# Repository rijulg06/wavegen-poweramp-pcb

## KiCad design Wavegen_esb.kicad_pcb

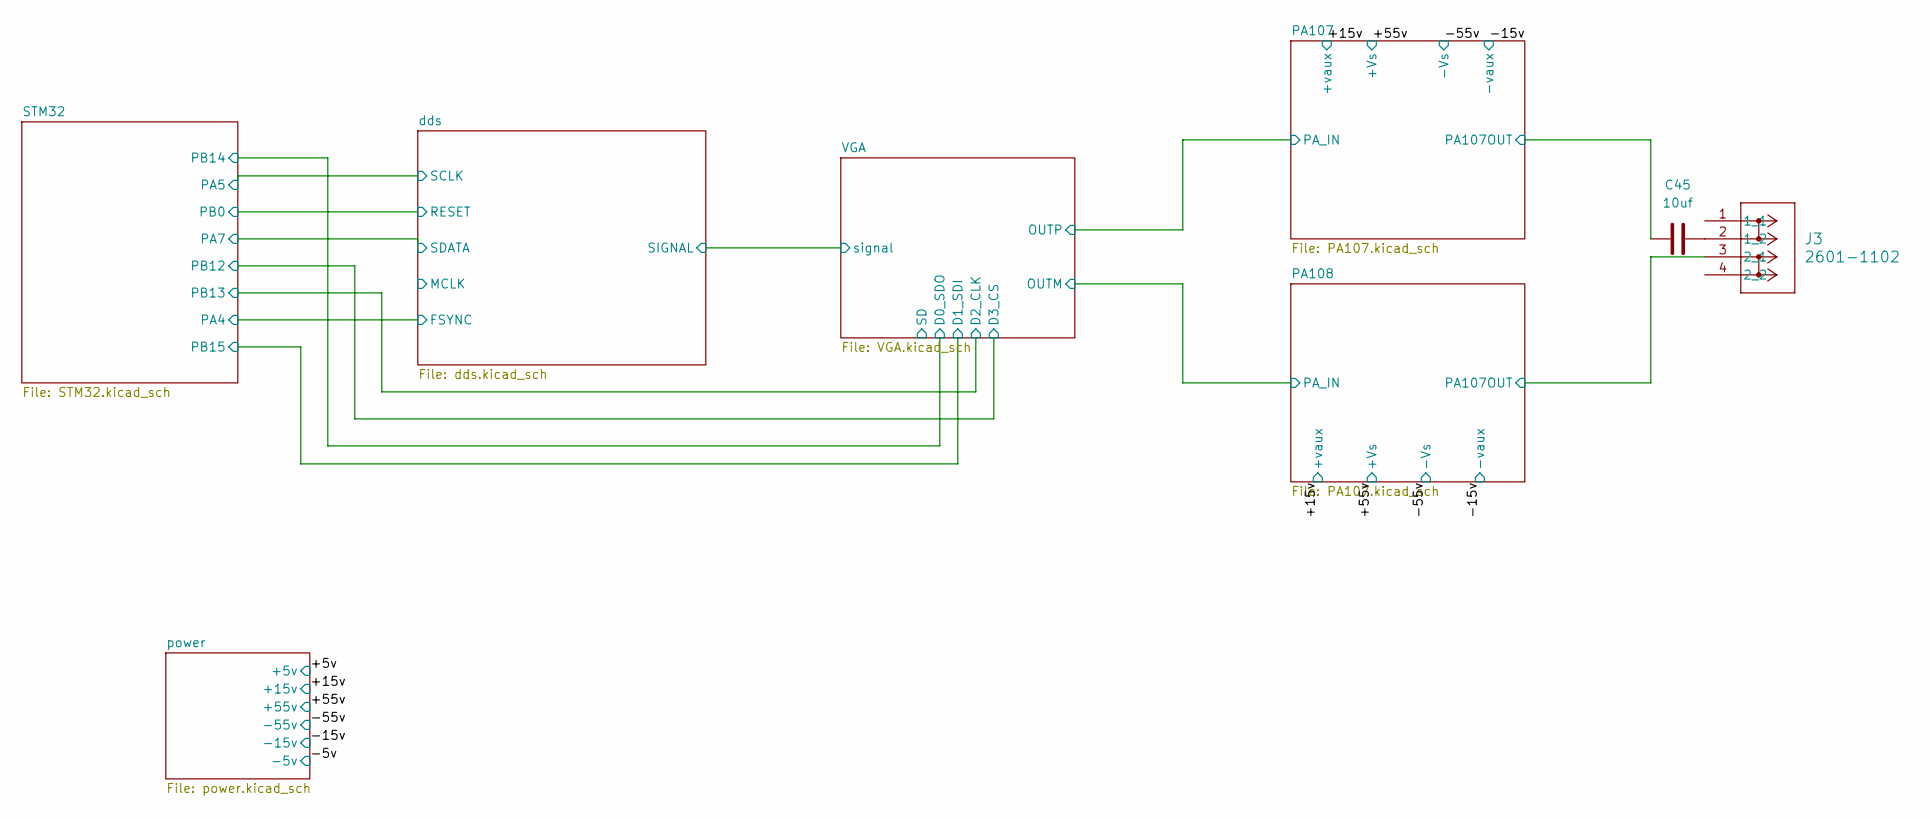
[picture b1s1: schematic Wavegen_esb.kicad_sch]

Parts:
C45: 10uf; CAPRR1500W80L2600T1150H2600
J3: 2601-1102; CONN2_2601-1102_WAG

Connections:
/PA107/PA107OUT: C45.2; also elsewhere on the board
/PA108/PA107OUT: J3.3 (2_1); also elsewhere on the board
unnamed: C45.1, J3.2 (1_2)

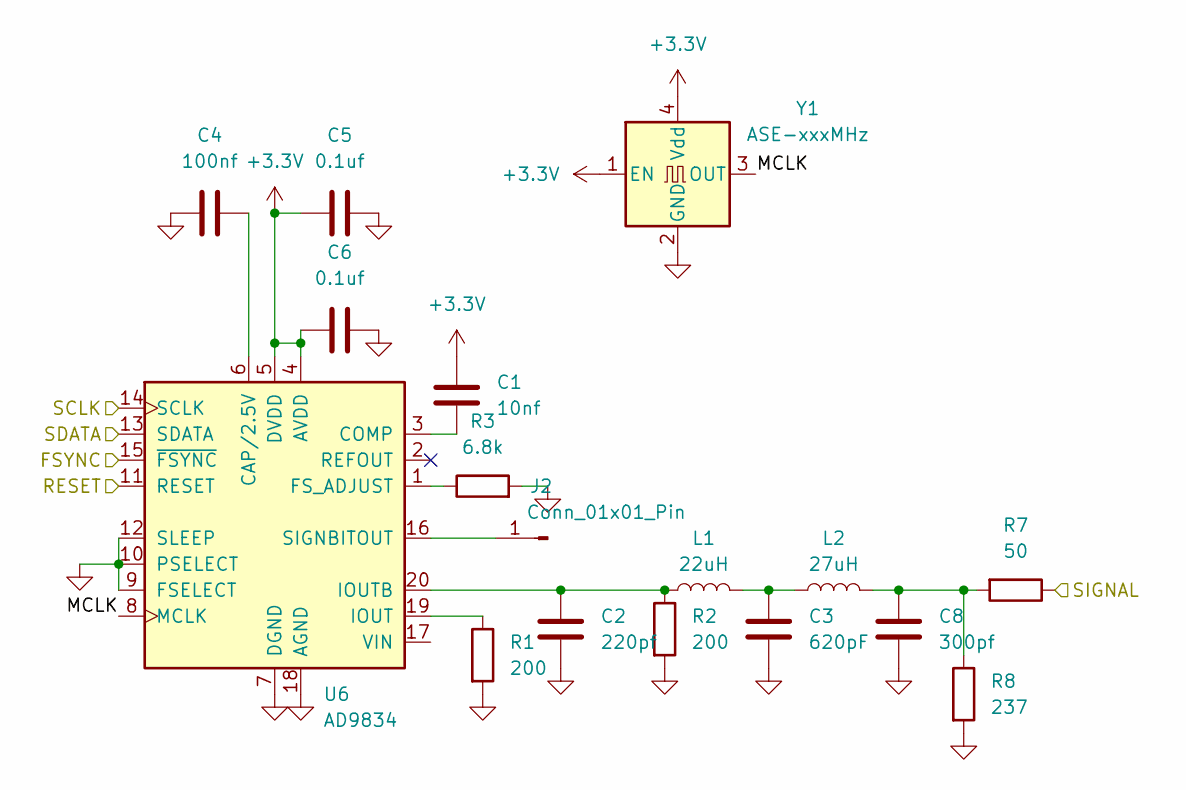
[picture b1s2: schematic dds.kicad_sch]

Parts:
C1: 10nf; C_0201_0603Metric
C2: 220pf; C_0201_0603Metric
C3: 620pF; C_0201_0603Metric
C4: 100nf; C_0201_0603Metric
C5, C6: 0.1uf; C_0201_0603Metric
C8: 300pf; C_0201_0603Metric
J2: Conn_01x01_Pin; TestPoint_Pad_1.5x1.5mm
L1: 22uH; IND_LSQM_B201616_TAY
L2: 27uH; IND_LSQM_B201616_TAY
R1, R2: 200; R_0201_0603Metric
R3: 6.8k; R_0201_0603Metric
R7: 50; R_0201_0603Metric
R8: 237; R_0201_0603Metric
U6: AD9834; TSSOP-20_4.4x6.5mm_P0.65mm
Y1: ASE-xxxMHz; Oscillator_SMD_Abracon_ASE-4Pin_3.2x2.5mm

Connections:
+3.3V: C1.2, C5.1, C6.1, U6.4 (AVDD), U6.5 (DVDD), Y1.1 (EN), Y1.4 (Vdd); also elsewhere on the board
/STM32/PA4: U6.15 (~FSYNC); also elsewhere on the board
/STM32/PA5: U6.14 (SCLK); also elsewhere on the board
/STM32/PA7: U6.13 (SDATA); also elsewhere on the board
/STM32/PB0: U6.11 (RESET); also elsewhere on the board
/VGA/signal: R7.1; also elsewhere on the board
/dds/MCLK: U6.8 (MCLK), Y1.3 (OUT)
GND: C2.1, C3.1, C4.1, C5.2, C6.2, C8.1, R1.2, R2.2, R3.2, R8.2, U6.7 (DGND), U6.9 (FSELECT), U6.10 (PSELECT), U6.12 (SLEEP), U6.18 (AGND), Y1.2 (GND); also elsewhere on the board
unnamed: C3.2, L1.2, L2.1
unnamed: C8.2, L2.2, R7.2, R8.1
unnamed: J2.1, U6.16 (SIGNBITOUT)
unnamed: C4.2, U6.6 (CAP/2.5V)
unnamed: C1.1, U6.3 (COMP)
unnamed: R3.1, U6.1 (FS_ADJUST)
unnamed: R1.1, U6.19 (IOUT)
unnamed: C2.2, L1.1, R2.1, U6.20 (IOUTB)

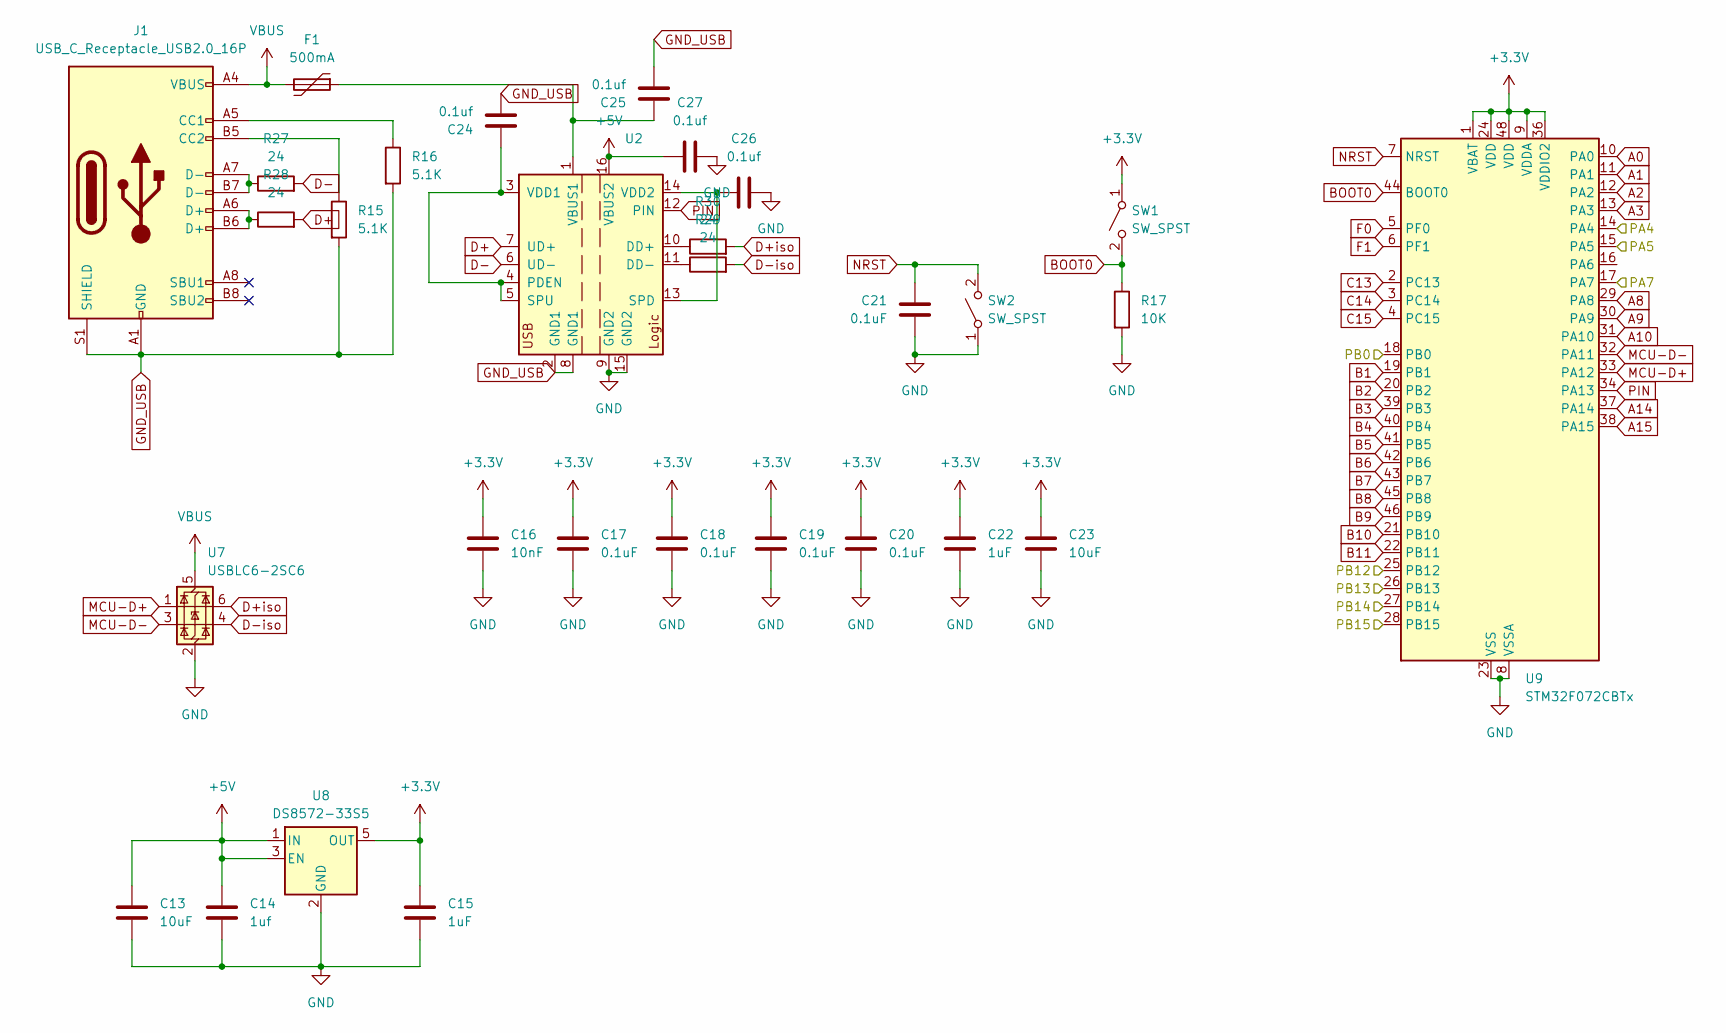
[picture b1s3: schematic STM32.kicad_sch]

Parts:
C13, C23: 10uF; C_0201_0603Metric
C14: 1uf; C_0201_0603Metric
C15, C22: 1uF; C_0201_0603Metric
C16: 10nF; C_0201_0603Metric
C17, C18, C19, C20, C21: 0.1uF; C_0201_0603Metric
C24, C25, C26, C27: 0.1uf; C_0201_0603Metric
F1: 500mA; Fuse_0805_2012Metric
J1: USB_C_Receptacle_USB2.0_16P; USB_C_Receptacle_GCT_USB4105-xx-A_16P_TopMnt_Horizontal
R15, R16: 5.1K; R_0201_0603Metric
R17: 10K; R_0805_2012Metric
R27, R28, R29, R30: 24; R_0201_0603Metric
SW1, SW2: SW_SPST; SW_SPST_B3U-1000P
U2: ADUM4160; SOIC-16W_7.5x10.3mm_P1.27mm
U7: USBLC6-2SC6; SOT-23-6
U8: DS8572-33S5; SOT-23-5
U9: STM32F072CBTx; LQFP-48_7x7mm_P0.5mm

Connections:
+3.3V: C15.1, C16.1, C17.1, C18.1, C19.1, C20.1, C22.1, C23.1, SW1.1 (A), U8.5 (OUT), U9.1 (VBAT), U9.9 (VDDA), U9.24 (VDD), U9.36 (VDDIO2), U9.48 (VDD); also elsewhere on the board
+5V: C13.1, C14.1, C27.2, U2.16 (VBUS2), U8.1 (IN), U8.3 (EN); also elsewhere on the board
/STM32/PA4: U9.14 (PA4); also elsewhere on the board
/STM32/PA5: U9.15 (PA5); also elsewhere on the board
/STM32/PA7: U9.17 (PA7); also elsewhere on the board
/STM32/PB0: U9.18 (PB0); also elsewhere on the board
/STM32/PB12: U9.25 (PB12); also elsewhere on the board
/STM32/PB13: U9.26 (PB13); also elsewhere on the board
/STM32/PB14: U9.27 (PB14); also elsewhere on the board
/STM32/PB15: U9.28 (PB15); also elsewhere on the board
A0: U9.10 (PA0)
A1: U9.11 (PA1)
A2: U9.12 (PA2)
A3: U9.13 (PA3)
A8: U9.29 (PA8)
A9: U9.30 (PA9)
A10: U9.31 (PA10)
A14: U9.37 (PA14)
A15: U9.38 (PA15)
B1: U9.19 (PB1)
B2: U9.20 (PB2)
B3: U9.39 (PB3)
B4: U9.40 (PB4)
B5: U9.41 (PB5)
B6: U9.42 (PB6)
B7: U9.43 (PB7)
B8: U9.45 (PB8)
B9: U9.46 (PB9)
B10: U9.21 (PB10)
B11: U9.22 (PB11)
BOOT0: R17.1, SW1.2 (B), U9.44 (BOOT0)
C13: U9.2 (PC13)
C14: U9.3 (PC14)
C15: U9.4 (PC15)
D+: R28.2, U2.7 (UD+)
D+iso: R30.2, U7.6 (I/O1)
D-: R27.2, U2.6 (UD-)
D-iso: R29.2, U7.4 (I/O2)
F0: U9.5 (PF0)
F1: U9.6 (PF1)
GND: C13.2, C14.2, C15.2, C16.2, C17.2, C18.2, C19.2, C20.2, C21.1, C22.2, C23.2, C26.1, C27.1, R17.2, SW2.1 (A), U2.9 (GND2), U2.15 (GND2), U7.2 (GND), U8.2 (GND), U9.8 (VSSA), U9.23 (VSS), U9.35 (VSS), U9.47 (VSS); also elsewhere on the board
GND_USB: C24.2, C25.2, J1.A1 (GND), J1.A12 (GND), J1.B1 (GND), J1.B12 (GND), J1.S1 (SHIELD), R15.2, R16.2, U2.2 (GND1), U2.8 (GND1)
MCU-D+: U7.1 (I/O1), U9.33 (PA12)
MCU-D-: U7.3 (I/O2), U9.32 (PA11)
NRST: C21.2, SW2.2 (B), U9.7 (NRST)
unnamed: J1.A5 (CC1), R16.1
unnamed: J1.B5 (CC2), R15.1
unnamed: J1.A6 (D+), J1.B6 (D+), R28.1
unnamed: J1.A7 (D-), J1.B7 (D-), R27.1
unnamed: R30.1, U2.10 (DD+)
unnamed: R29.1, U2.11 (DD-)
unnamed: C24.1, U2.3 (VDD1), U2.4 (PDEN), U2.5 (SPU)
unnamed: C26.2, U2.13 (SPD), U2.14 (VDD2)
unnamed: C25.1, F1.1, U2.1 (VBUS1)
PIN: U2.12 (PIN), U9.34 (PA13)
VBUS: F1.2, J1.A4 (VBUS), J1.A9 (VBUS), J1.B4 (VBUS), J1.B9 (VBUS), U7.5 (VBUS)

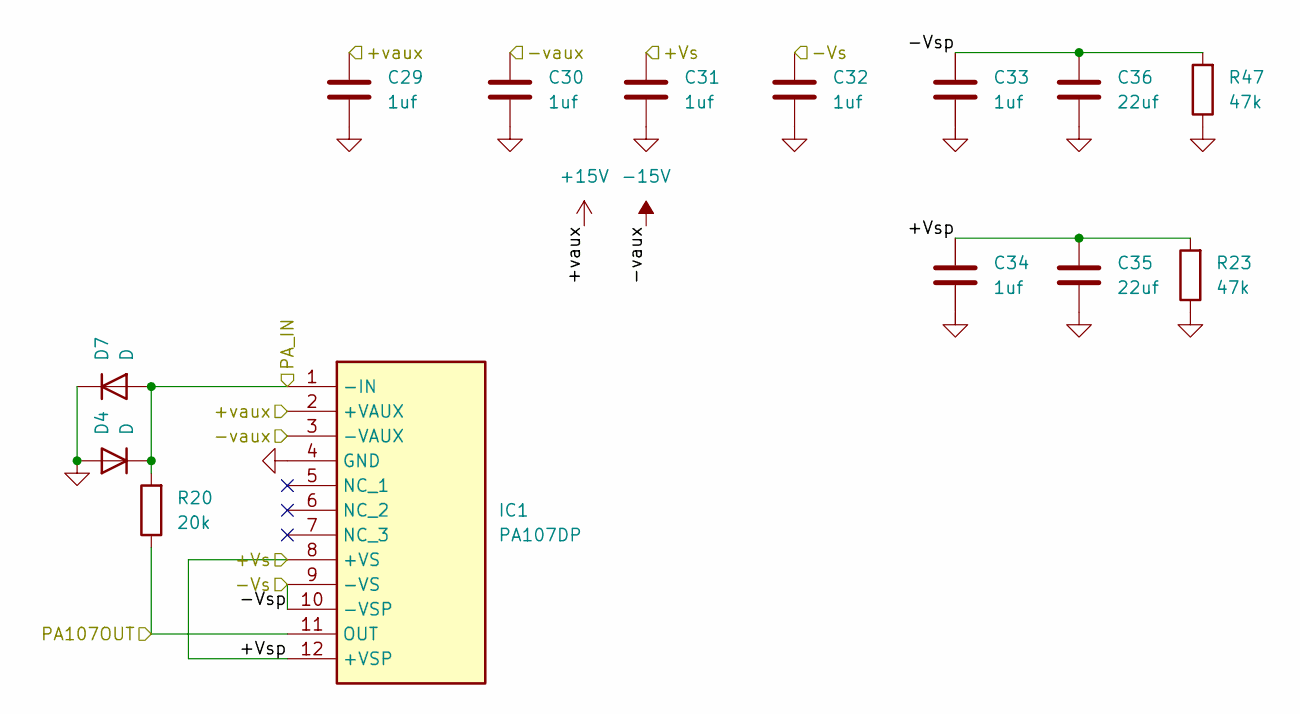
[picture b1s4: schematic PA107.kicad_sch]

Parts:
C29, C30, C31, C32, C33, C34: 1uf; C_0805_2012Metric
C35, C36: 22uf; CP_Radial_D6.3mm_P2.50mm
D4, D7: D
IC1: PA107DP; Manufacturer_Part_Number PA107DP; Mouser Part Number 137-PA107DP
R20: 20k; R_0805_2012Metric
R23, R47: 47k; R_0805_2012Metric

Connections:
+15V: C29.2, IC1.2 (+VAUX); also elsewhere on the board
-15V: C30.2, IC1.3 (-VAUX); also elsewhere on the board
/+55v: C31.2, C34.2, C35.2, IC1.8 (+VS), IC1.12 (+VSP), R23.2; also elsewhere on the board
/-55v: C32.2, C33.2, C36.2, IC1.9 (-VS), IC1.10 (-VSP), R47.2; also elsewhere on the board
/PA107/PA107OUT: IC1.11 (OUT), R20.1; also elsewhere on the board
/PA107/PA_IN: IC1.1 (-IN), R20.2; also elsewhere on the board
GND: C29.1, C30.1, C31.1, C32.1, C33.1, C34.1, C35.1, C36.1, D4.2 (A), D7.1 (K), IC1.4 (GND), R23.1, R47.1; also elsewhere on the board

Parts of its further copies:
C37, C38, C39, C40, C41, C42: 1uf; C_0805_2012Metric
C43, C44: 22uf; CP_Radial_D6.3mm_P2.50mm
IC2: PA107DP; Manufacturer_Part_Number PA107DP; Mouser Part Number 137-PA107DP
R21: 20k; R_0805_2012Metric
R22, R24: 47k; R_0805_2012Metric

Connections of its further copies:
+15V: C37.2, IC2.2 (+VAUX); also elsewhere on the board
-15V: C38.2, IC2.3 (-VAUX); also elsewhere on the board
/+55v: C39.2, C42.2, C44.2, IC2.8 (+VS), IC2.12 (+VSP), R24.2; also elsewhere on the board
/-55v: C40.2, C41.2, C43.2, IC2.9 (-VS), IC2.10 (-VSP), R22.2; also elsewhere on the board
/PA108/PA107OUT: IC2.11 (OUT), R21.1; also elsewhere on the board
/PA108/PA_IN: IC2.1 (-IN), R21.2; also elsewhere on the board
GND: C37.1, C38.1, C39.1, C40.1, C41.1, C42.1, C43.1, C44.1, IC2.4 (GND), R22.1, R24.1; also elsewhere on the board

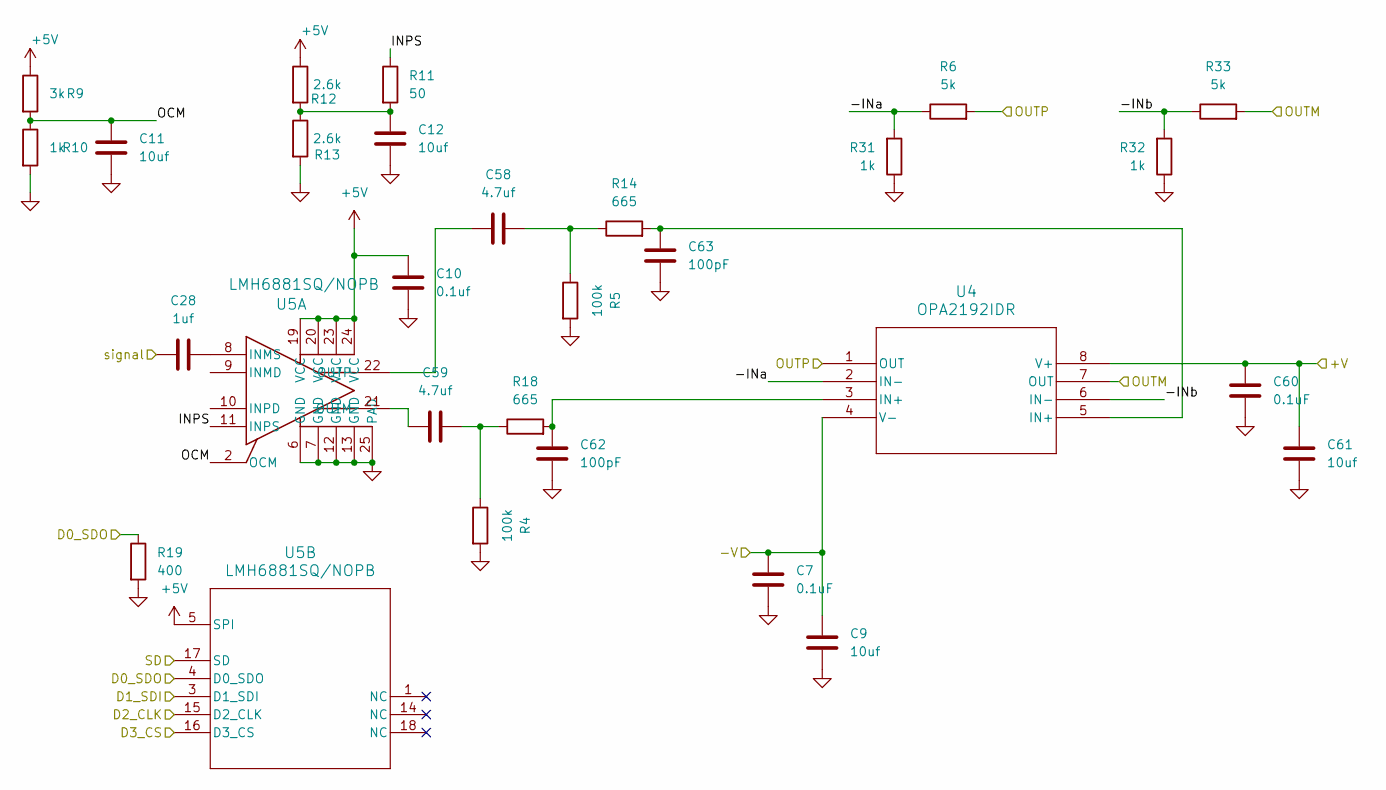
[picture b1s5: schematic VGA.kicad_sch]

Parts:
C7, C60: 0.1uF; C_0201_0603Metric
C9, C61: 10uf; C_Radial_D5.0mm_H5.0mm_P2.00mm
C10: 0.1uf; C_0201_0603Metric
C11, C12: 10uf; C_0201_0603Metric
C28: 1uf; C_0201_0603Metric
C58, C59: 4.7uf; C_0805_2012Metric
C62, C63: 100pF; C_0805_2012Metric
R4, R5: 100k; R_0805_2012Metric
R6, R33: 5k; R_0805_2012Metric
R9: 3k; R_0201_0603Metric
R10: 1k; R_0201_0603Metric
R11: 50; R_0201_0603Metric
R12, R13: 2.6k; R_0201_0603Metric
R14, R18: 665; R_0805_2012Metric
R19: 400; R_0201_0603Metric
R31, R32: 1k; R_0805_2012Metric
U4: OPA2192IDR; DGK0008A_N_TEX
U5: LMH6881SQ/NOPB; RTW0024A

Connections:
+5V: C10.2, R9.1, R12.1, U5.5 (SPI), U5.19 (VCC), U5.20 (VCC), U5.23 (VCC), U5.24 (VCC); also elsewhere on the board
/PA107/PA_IN: R6.2, U4.1 (OUT); also elsewhere on the board
/PA108/PA_IN: R33.2, U4.7 (OUT); also elsewhere on the board
/STM32/PB12: U5.16 (D3_CS); also elsewhere on the board
/STM32/PB13: U5.15 (D2_CLK); also elsewhere on the board
/STM32/PB14: R19.1, U5.4 (D0_SDO); also elsewhere on the board
/STM32/PB15: U5.3 (D1_SDI); also elsewhere on the board
/VGA/+V: C60.1, C61.1, U4.8 (V+)
/VGA/-INa: R6.1, R31.2, U4.2 (IN-)
/VGA/-INb: R32.2, R33.1, U4.6 (IN-)
/VGA/-V: C7.1, C9.1, U4.4 (V-)
/VGA/INPS: R11.1, U5.11 (INPS)
/VGA/OCM: C11.2, R9.2, R10.1, U5.2 (OCM)
/VGA/SD: U5.17 (SD)
/VGA/signal: C28.1; also elsewhere on the board
GND: C7.2, C9.2, C10.1, C11.1, C12.2, C60.2, C61.2, C62.2, C63.2, R4.2, R5.2, R10.2, R13.2, R19.2, R31.1, R32.1, U5.6 (GND), U5.7 (GND), U5.12 (GND), U5.13 (GND), U5.25 (PAD); also elsewhere on the board
unnamed: C12.1, R11.2, R12.2, R13.1
unnamed: C58.1, R5.1, R14.1
unnamed: C59.1, R4.1, R18.1
unnamed: C62.1, R18.2, U4.3 (IN+)
unnamed: C63.1, R14.2, U4.5 (IN+)
unnamed: C28.2, U5.8 (INMS)
unnamed: C59.2, U5.21 (OUTM)
unnamed: C58.2, U5.22 (OUTP)

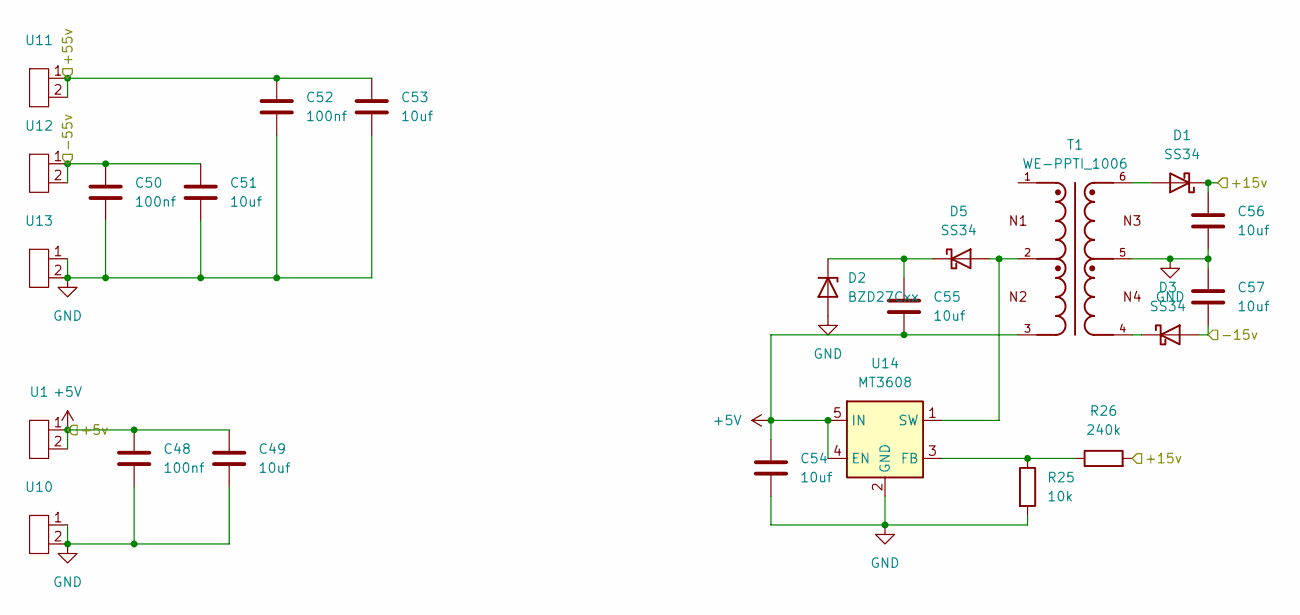
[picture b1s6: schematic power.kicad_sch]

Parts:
C48, C50, C52: 100nf; C_0201_0603Metric
C49, C51, C53, C55, C56, C57: 10uf; C_0805_2012Metric
C54: 10uf; C_0201_0603Metric
D1, D3, D5: SS34; D_SMA
D2: BZD27Cxx; SOT-23
R25: 10k; R_0201_0603Metric
R26: 240k; R_0201_0603Metric
T1: WE-PPTI_1006; WE-PPTI_1006_L10.2W6.73H4.19
U1, U10, U11, U12, U13: Untitled
U14: MT3608; SOT-23-6

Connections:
+5V: C48.1, C49.1, C54.1, C55.2, T1.3, U1.1, U1.2, U14.4 (EN), U14.5 (IN); also elsewhere on the board
+15V: C56.1, D1.1 (K), R26.2; also elsewhere on the board
-15V: C57.2, D3.2 (A); also elsewhere on the board
/+55v: C52.1, C53.1, U11.1, U11.2; also elsewhere on the board
/-55v: C50.1, C51.1, U12.1, U12.2; also elsewhere on the board
GND: C48.2, C49.2, C50.2, C51.2, C52.2, C53.2, C54.2, C56.2, C57.1, D2.2 (A), R25.2, T1.5, U10.1, U10.2, U13.1, U13.2, U14.2 (GND); also elsewhere on the board
unnamed: D1.2 (A), T1.6
unnamed: C55.1, D2.1 (K), D5.1 (K)
unnamed: D3.1 (K), T1.4
unnamed: D5.2 (A), T1.2, U14.1 (SW)
unnamed: R25.1, R26.1, U14.3 (FB)

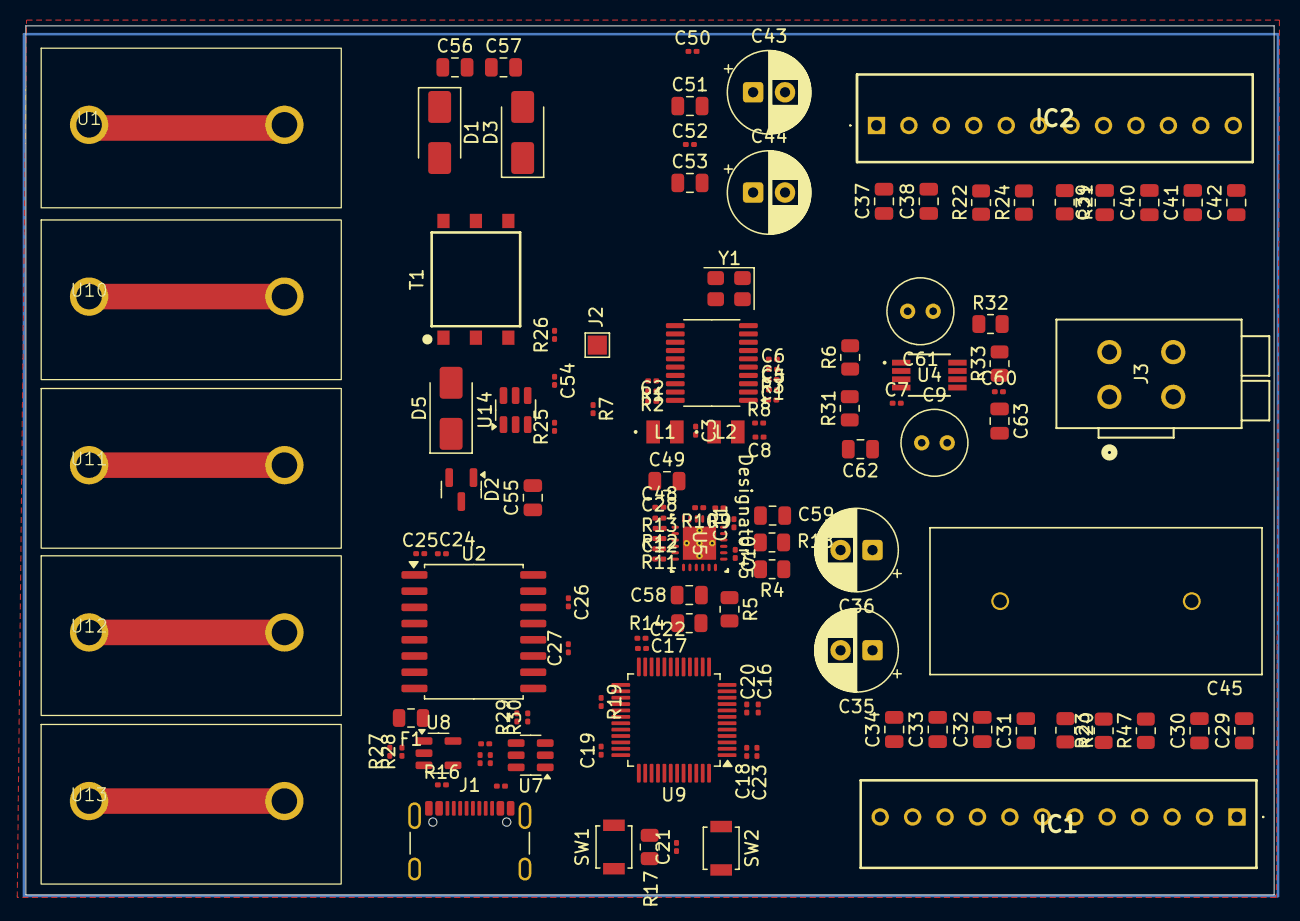
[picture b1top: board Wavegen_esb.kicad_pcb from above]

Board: 4 copper layers, 97.8 x 68.0 mm, 124 parts (0 on the bottom side), 69 nets.
